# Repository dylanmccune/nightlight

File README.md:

<picture>
  <source media="(prefers-color-scheme: dark)" srcset="./assets/logo_dark.svg">
  <source media="(prefers-color-scheme: light)" srcset="./assets/logo_light.svg">
  
</picture>

# Night light
A little light that turns on when it gets dark so the monsters under the bed can't hurt you

Just an LED with a photoresistor that turns on when it gets dark (plus some other parts).

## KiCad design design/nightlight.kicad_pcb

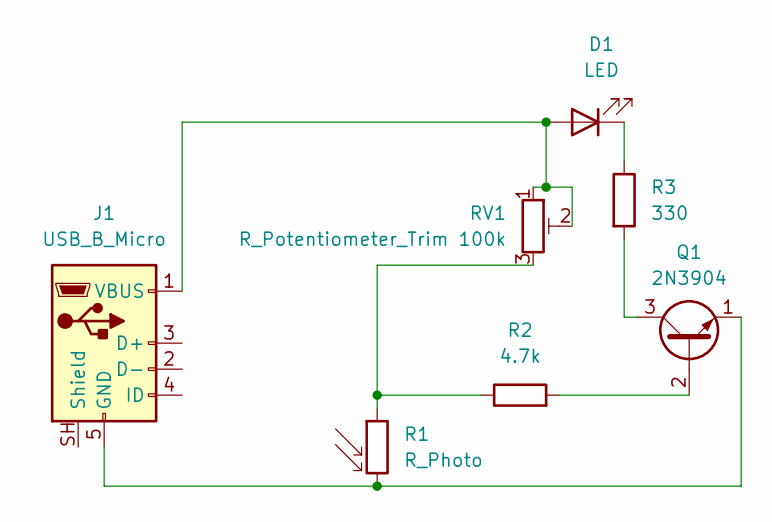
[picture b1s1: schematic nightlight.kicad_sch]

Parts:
D1: LED; LED_D5.0mm
J1: USB_B_Micro; USB3145-30-1-A
Q1: 2N3904; TO-92_Inline
R1: R_Photo; PHODET_PDV-P8103
R2: 4.7k; R_Axial_DIN0207_L6.3mm_D2.5mm_P7.62mm_Horizontal
R3: 330; R_Axial_DIN0207_L6.3mm_D2.5mm_P7.62mm_Horizontal
RV1: R_Potentiometer_Trim 100k; TRIM_3306F-1-104

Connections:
unnamed: D1.2 (A), J1.1 (VBUS), RV1.1, RV1.2
unnamed: D1.1 (K), R3.1
unnamed: J1.5 (GND), Q1.1 (E), R1.2
unnamed: Q1.2 (B), R2.2
unnamed: Q1.3 (C), R3.2
unnamed: R1.1, R2.1, RV1.3

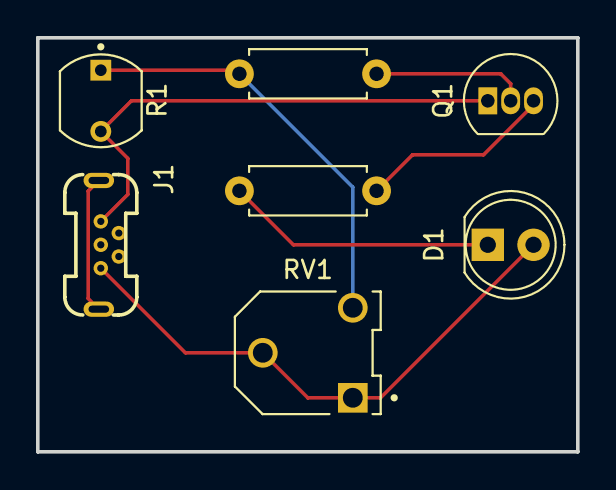
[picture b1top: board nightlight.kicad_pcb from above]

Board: 2 copper layers, 30.0 x 23.0 mm, 7 parts (0 on the bottom side), 6 nets.
